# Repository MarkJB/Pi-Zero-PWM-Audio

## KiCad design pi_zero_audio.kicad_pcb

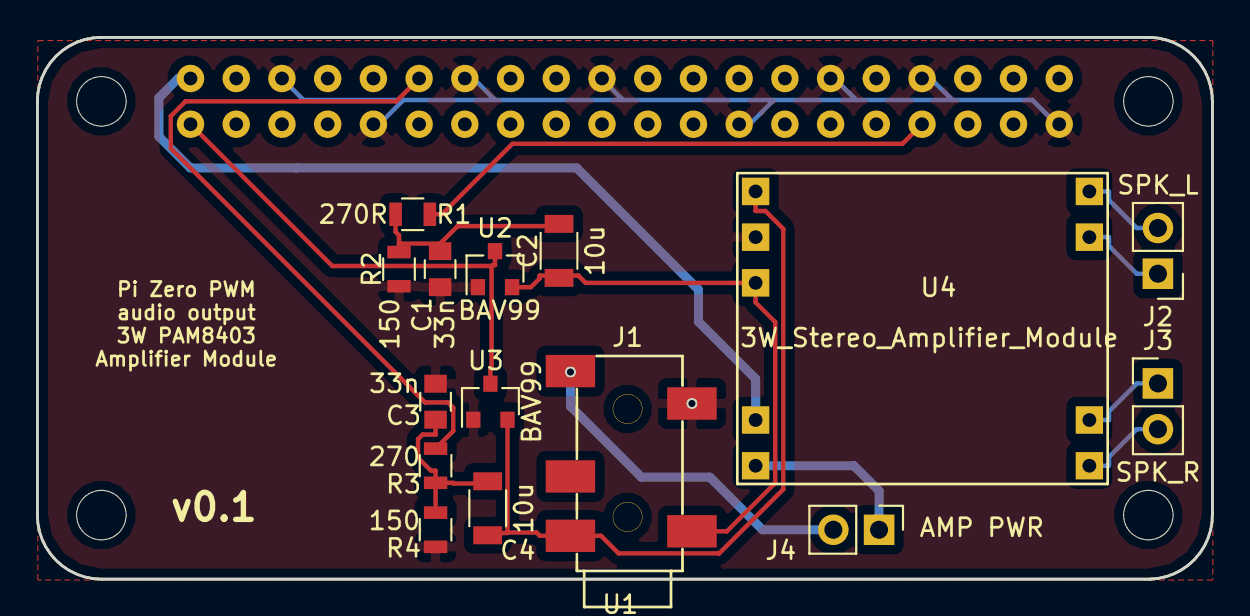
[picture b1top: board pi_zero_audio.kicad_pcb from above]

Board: 2 copper layers, 65.3 x 30.1 mm, 16 parts (0 on the bottom side), 15 nets.

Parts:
C1, C3: 33n; C_0805
C2, C4: 10u; C_1206
J1: CONN_01X05; SMT_3.5mm_Stereo_jack_5_pin
J2: SPK_L; Pin_Header_Straight_1x02_Pitch2.54mm
J3: SPK_R; Pin_Header_Straight_1x02_Pitch2.54mm
J4: AMP PWR; Pin_Header_Straight_1x02_Pitch2.54mm
R1: 270R; R_0805
R2, R4: 150; R_0805
R3: 270; R_0805
U1: PiZero; Pi_Zero
U2, U3: BAV99; SOT-23
U4: 3W_Stereo_Amplifier_Module; 3W_Stereo_amplifier_module

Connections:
/L: C4.1, J1.1, U3.2, U4.1
/R: C2.1, J1.4, U2.2, U4.3
unnamed: C1.1, C2.2, R1.1, R2.1
unnamed: C1.2, C3.2, J1.2, R2.2, R4.2, U1.6, U1.9, U1.14, U1.20, U1.25, U1.30, U1.34, U1.39, U2.1, U3.1, U4.2
unnamed: C3.1, C4.2, R3.1, R4.1
unnamed: J1.5, J4.2
unnamed: J2.1, U4.8
unnamed: J2.2, U4.9
unnamed: J3.1, U4.7
unnamed: J3.2, U4.6
unnamed: J4.1, U4.5
unnamed: R1.2, U1.33
unnamed: R3.2, U1.12
unnamed: U1.1, U2.3, U3.3
unnamed: U1.2, U4.4

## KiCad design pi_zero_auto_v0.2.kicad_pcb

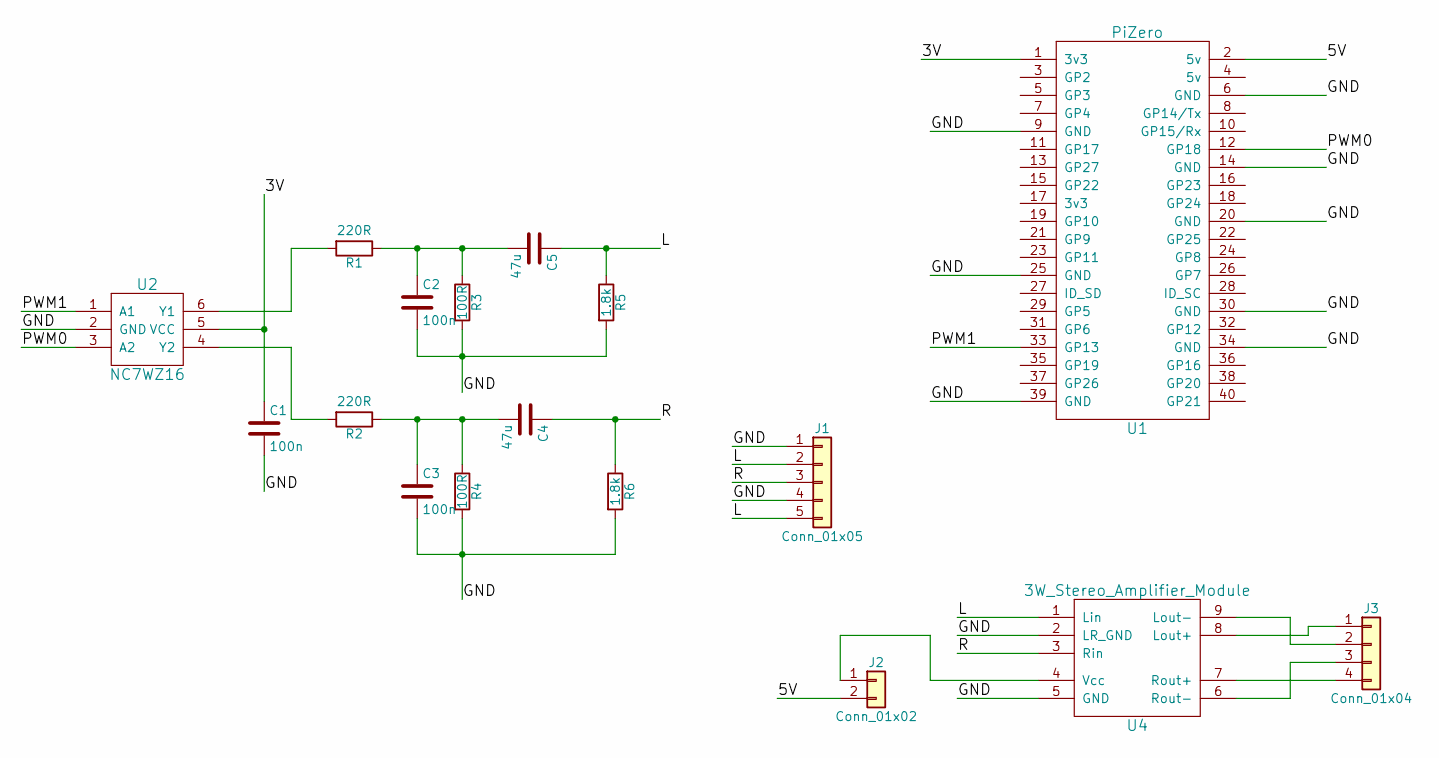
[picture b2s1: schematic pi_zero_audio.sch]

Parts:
C1, C2, C3: 100n; C_0805
C4, C5: 47u; C_1206
J1: Conn_01x05; SMT_3.5mm_Stereo_jack_5_pin
J2: Conn_01x02; Pin_Header_Straight_1x02_Pitch2.54mm
J3: Conn_01x04; TerminalBlock_bornier-4_P5.08mm
R1, R2: 220R; R_0805
R3, R4: 100R; R_0805
R5, R6: 1.8k; R_0805
U1: PiZero; Pi_Zero
U2: NC7WZ16; SC70-6pin
U4: 3W_Stereo_Amplifier_Module; 3W_Stereo_amplifier_module

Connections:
/3V: C1.1, U1.1 (3v3), U2.5 (VCC)
/5V: J2.2, U1.2 (5v)
/GND: C1.2, C2.2, C3.2, J1.1, J1.4, R3.2, R4.2, R5.2, R6.2, U1.6 (GND), U1.9 (GND), U1.14 (GND), U1.20 (GND), U1.25 (GND), U1.30 (GND), U1.34 (GND), U1.39 (GND), U2.2 (GND), U4.2 (LR_GND), U4.5 (GND)
/L: C5.1, J1.2, J1.5, R5.1, U4.1 (Lin)
/PWM0: U1.12 (GP18), U2.3 (A2)
/PWM1: U1.33 (GP13), U2.1 (A1)
/R: C4.1, J1.3, R6.1, U4.3 (Rin)
unnamed: C2.1, C5.2, R1.1, R3.1
unnamed: C3.1, C4.2, R2.1, R4.1
unnamed: J2.1, U4.4 (Vcc)
unnamed: J3.1, U4.8 (Lout+)
unnamed: J3.2, U4.9 (Lout-)
unnamed: J3.3, U4.6 (Rout-)
unnamed: J3.4, U4.7 (Rout+)
unnamed: R1.2, U2.6 (Y1)
unnamed: R2.2, U2.4 (Y2)

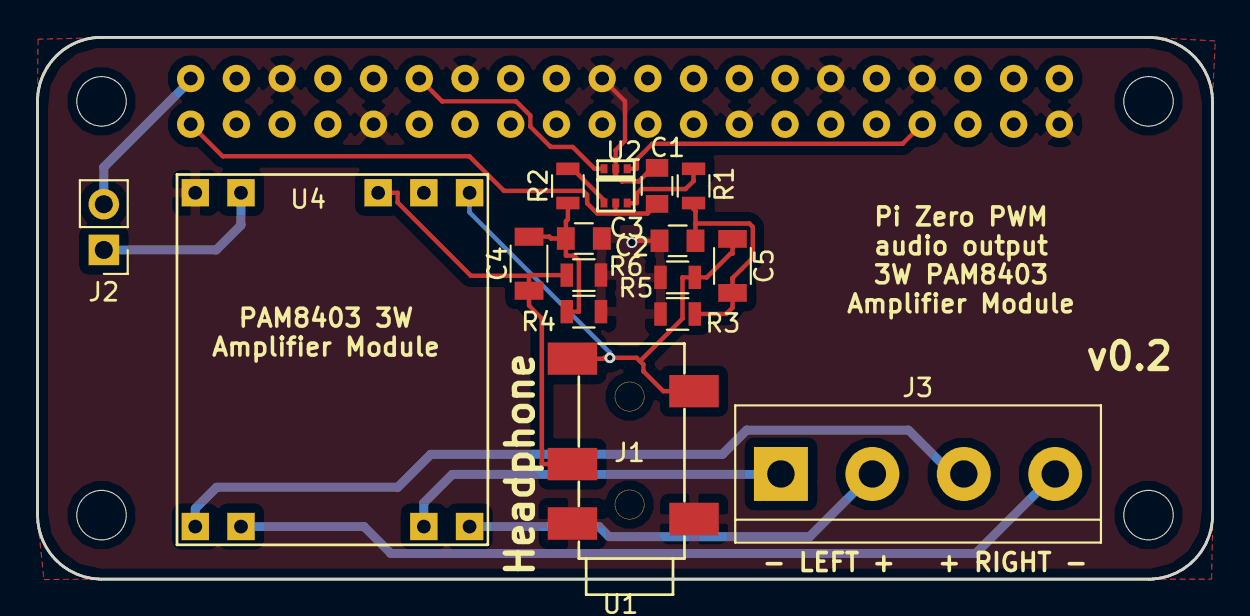
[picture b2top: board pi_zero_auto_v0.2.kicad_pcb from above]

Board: 2 copper layers, 65.3 x 30.1 mm, 17 parts (0 on the bottom side), 16 nets.

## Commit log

2020-12-22 Publish source to github
